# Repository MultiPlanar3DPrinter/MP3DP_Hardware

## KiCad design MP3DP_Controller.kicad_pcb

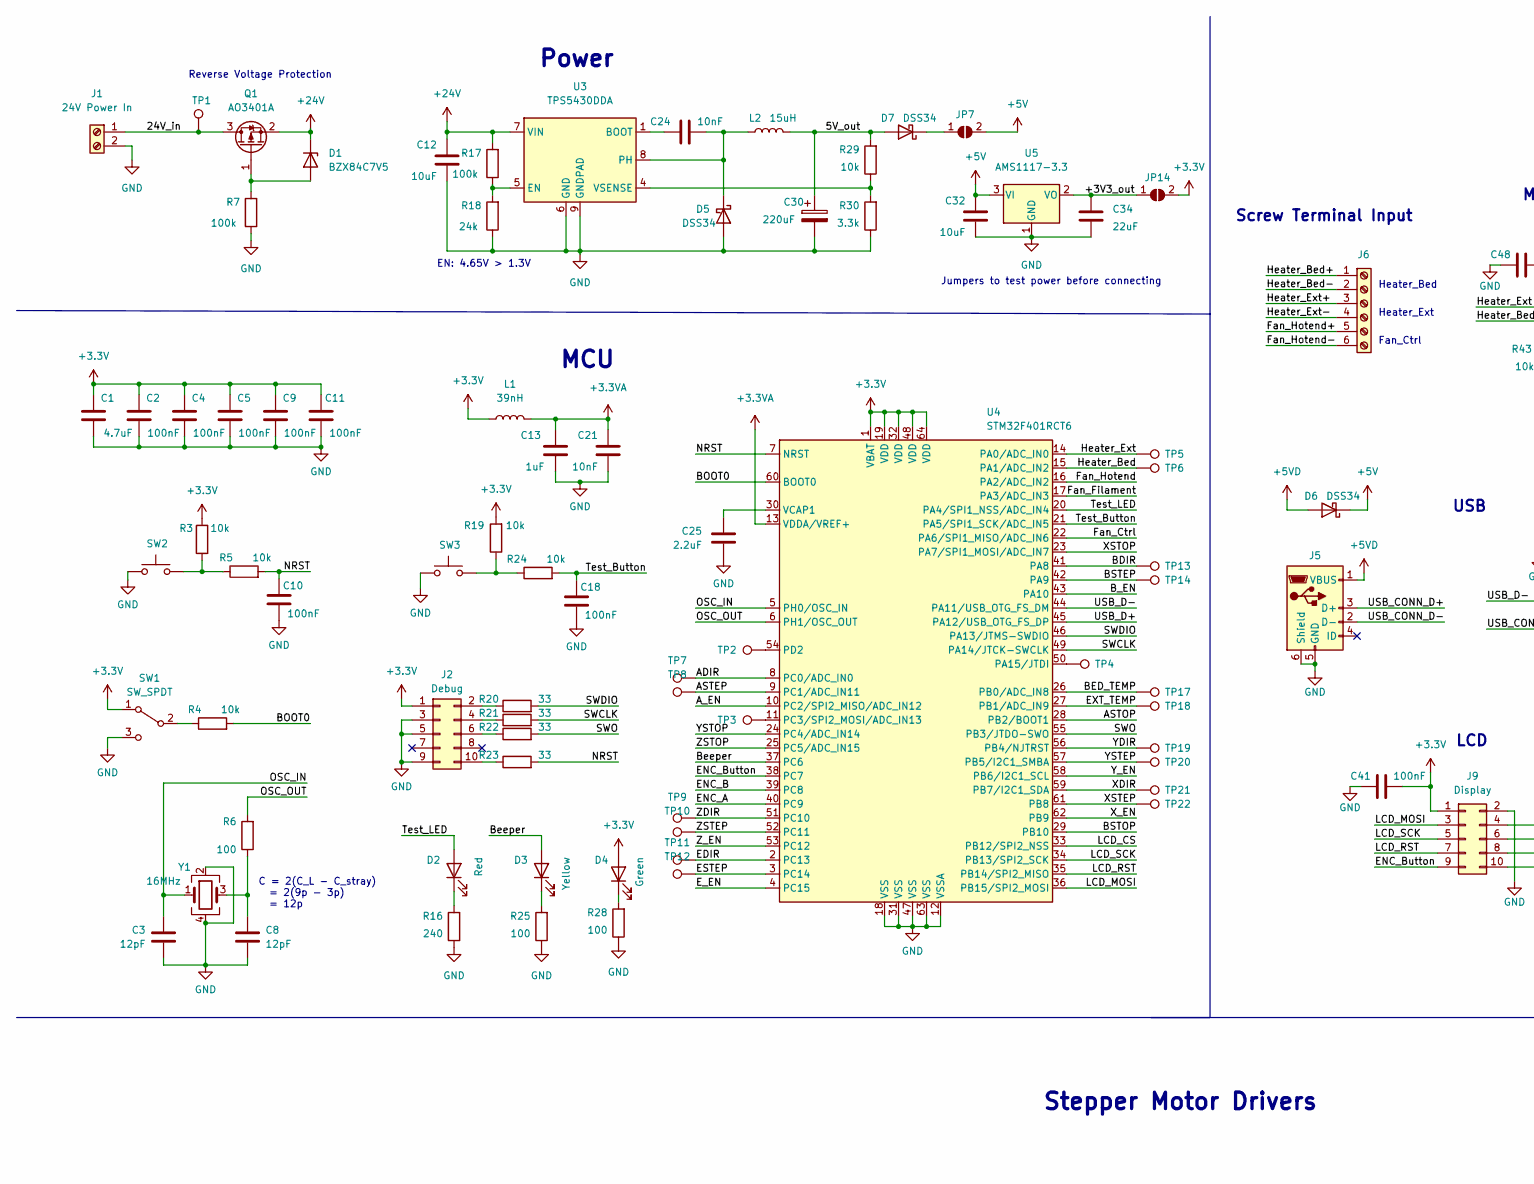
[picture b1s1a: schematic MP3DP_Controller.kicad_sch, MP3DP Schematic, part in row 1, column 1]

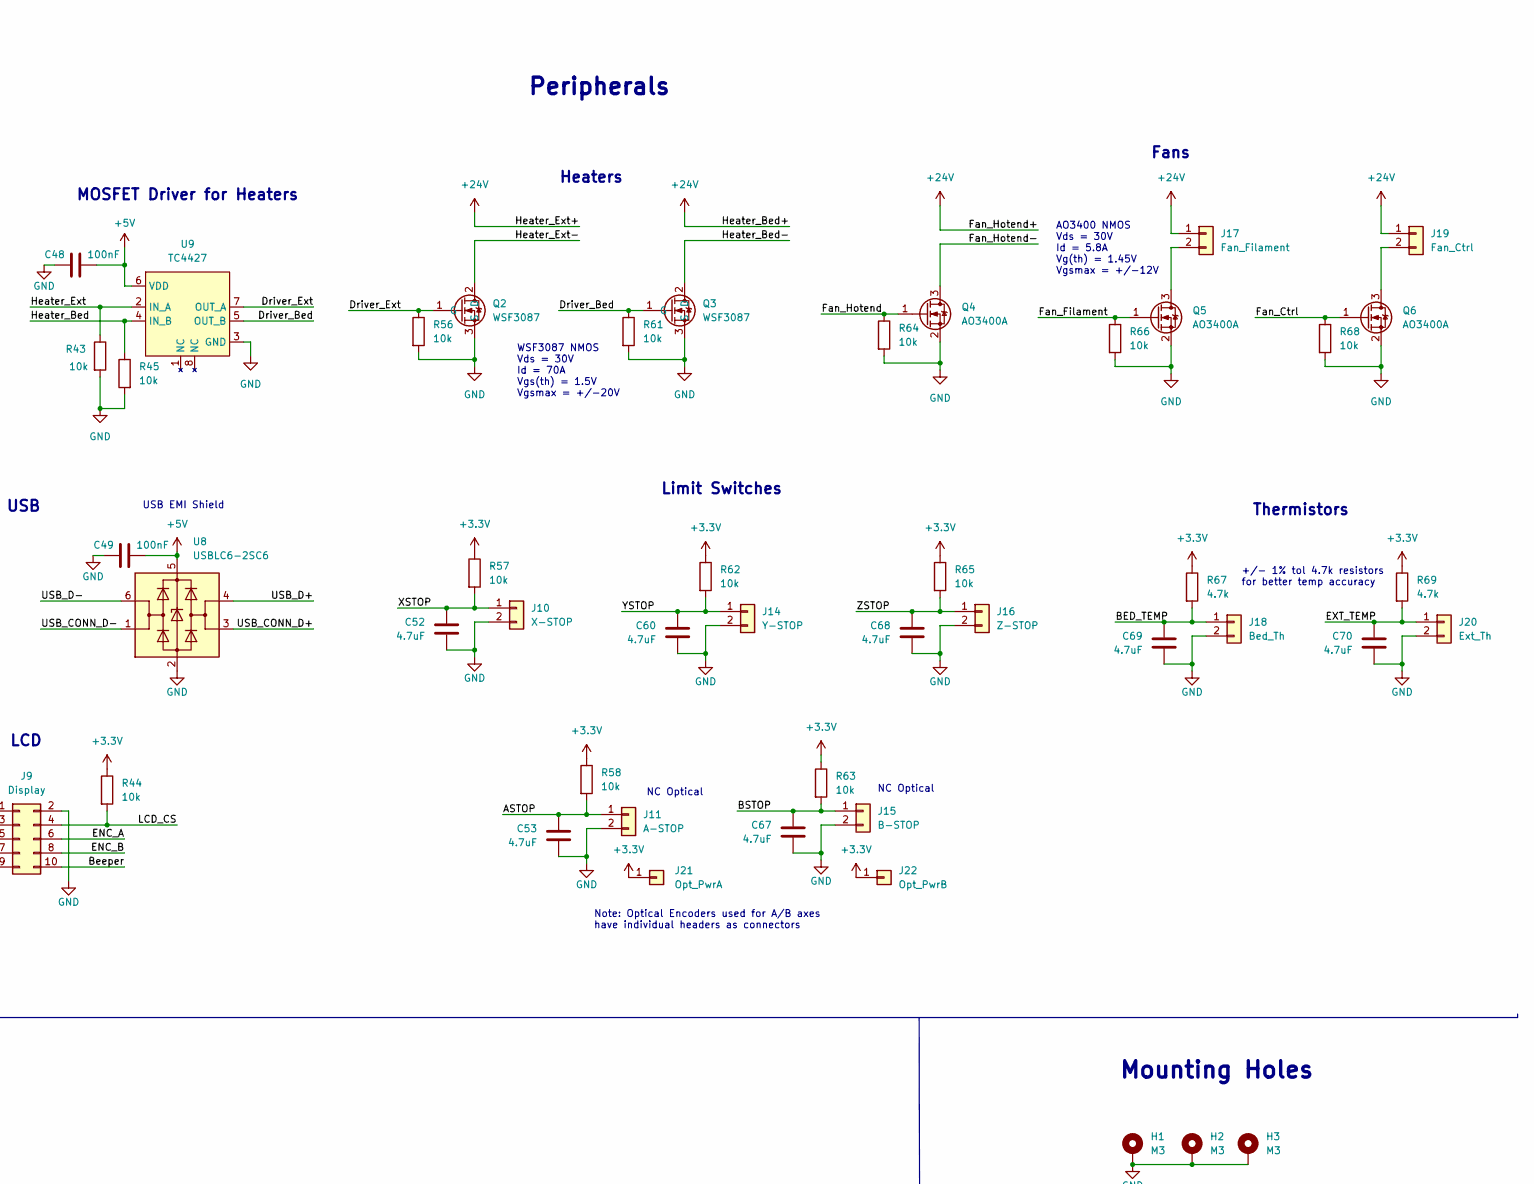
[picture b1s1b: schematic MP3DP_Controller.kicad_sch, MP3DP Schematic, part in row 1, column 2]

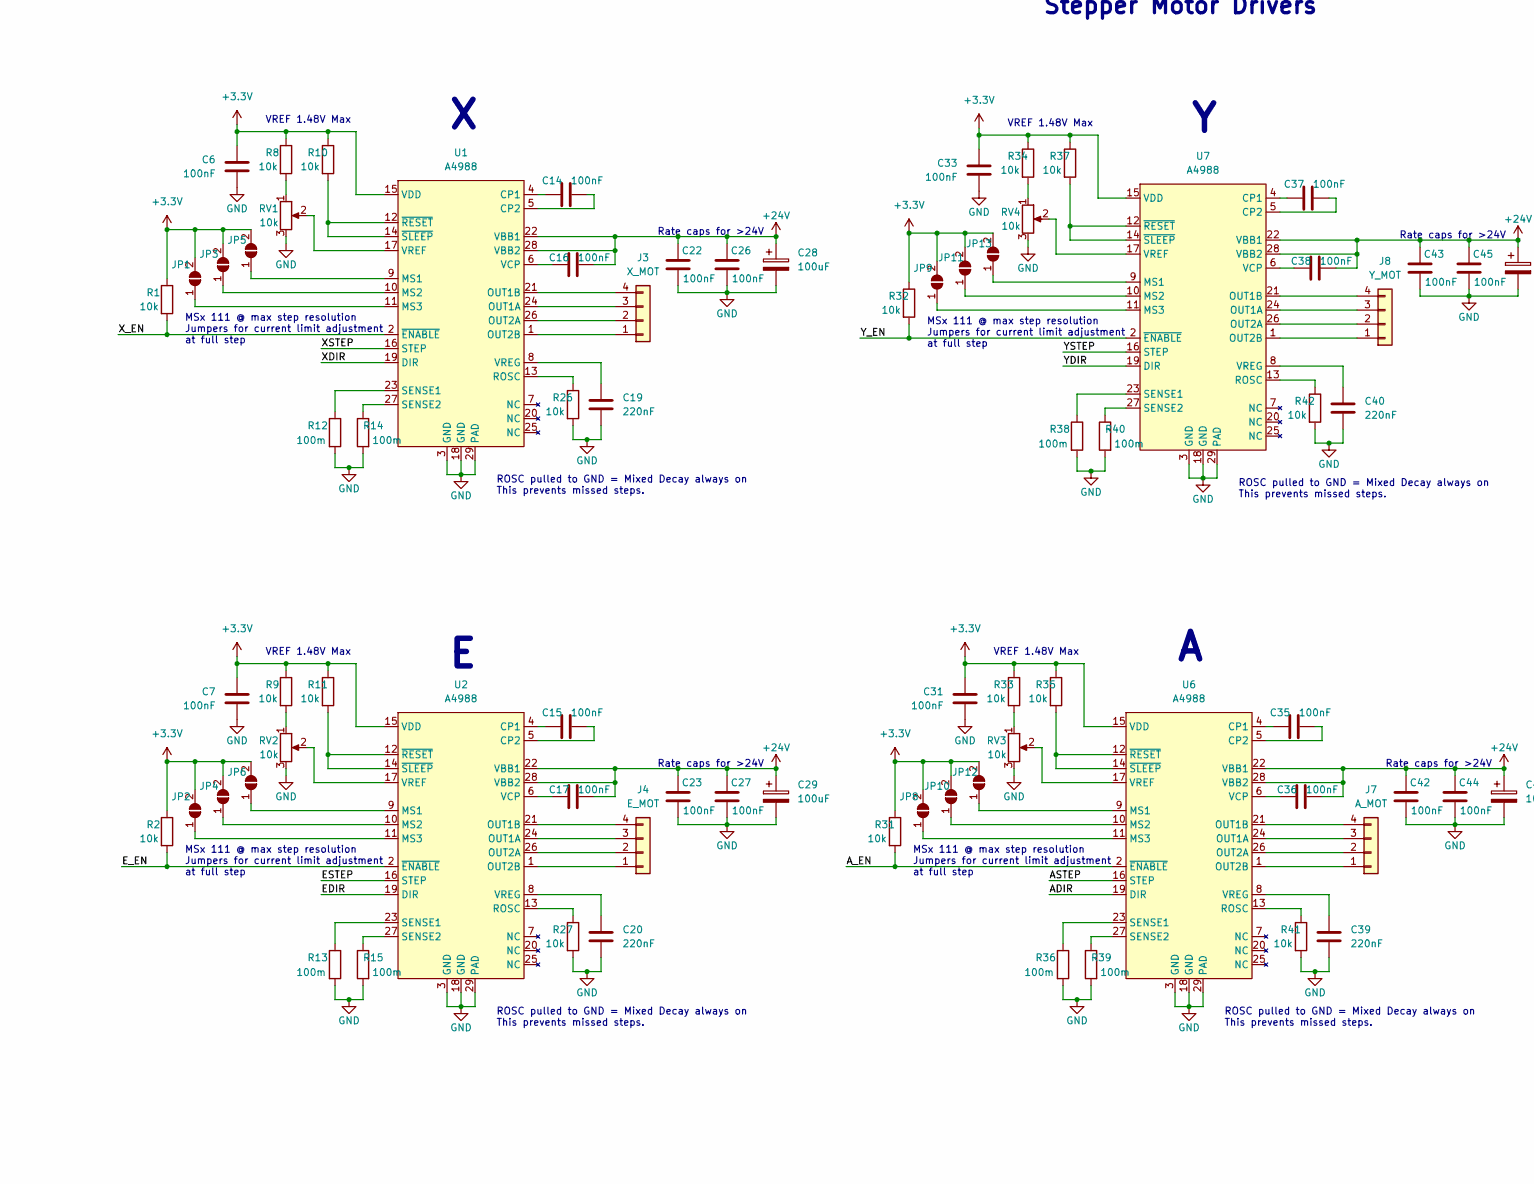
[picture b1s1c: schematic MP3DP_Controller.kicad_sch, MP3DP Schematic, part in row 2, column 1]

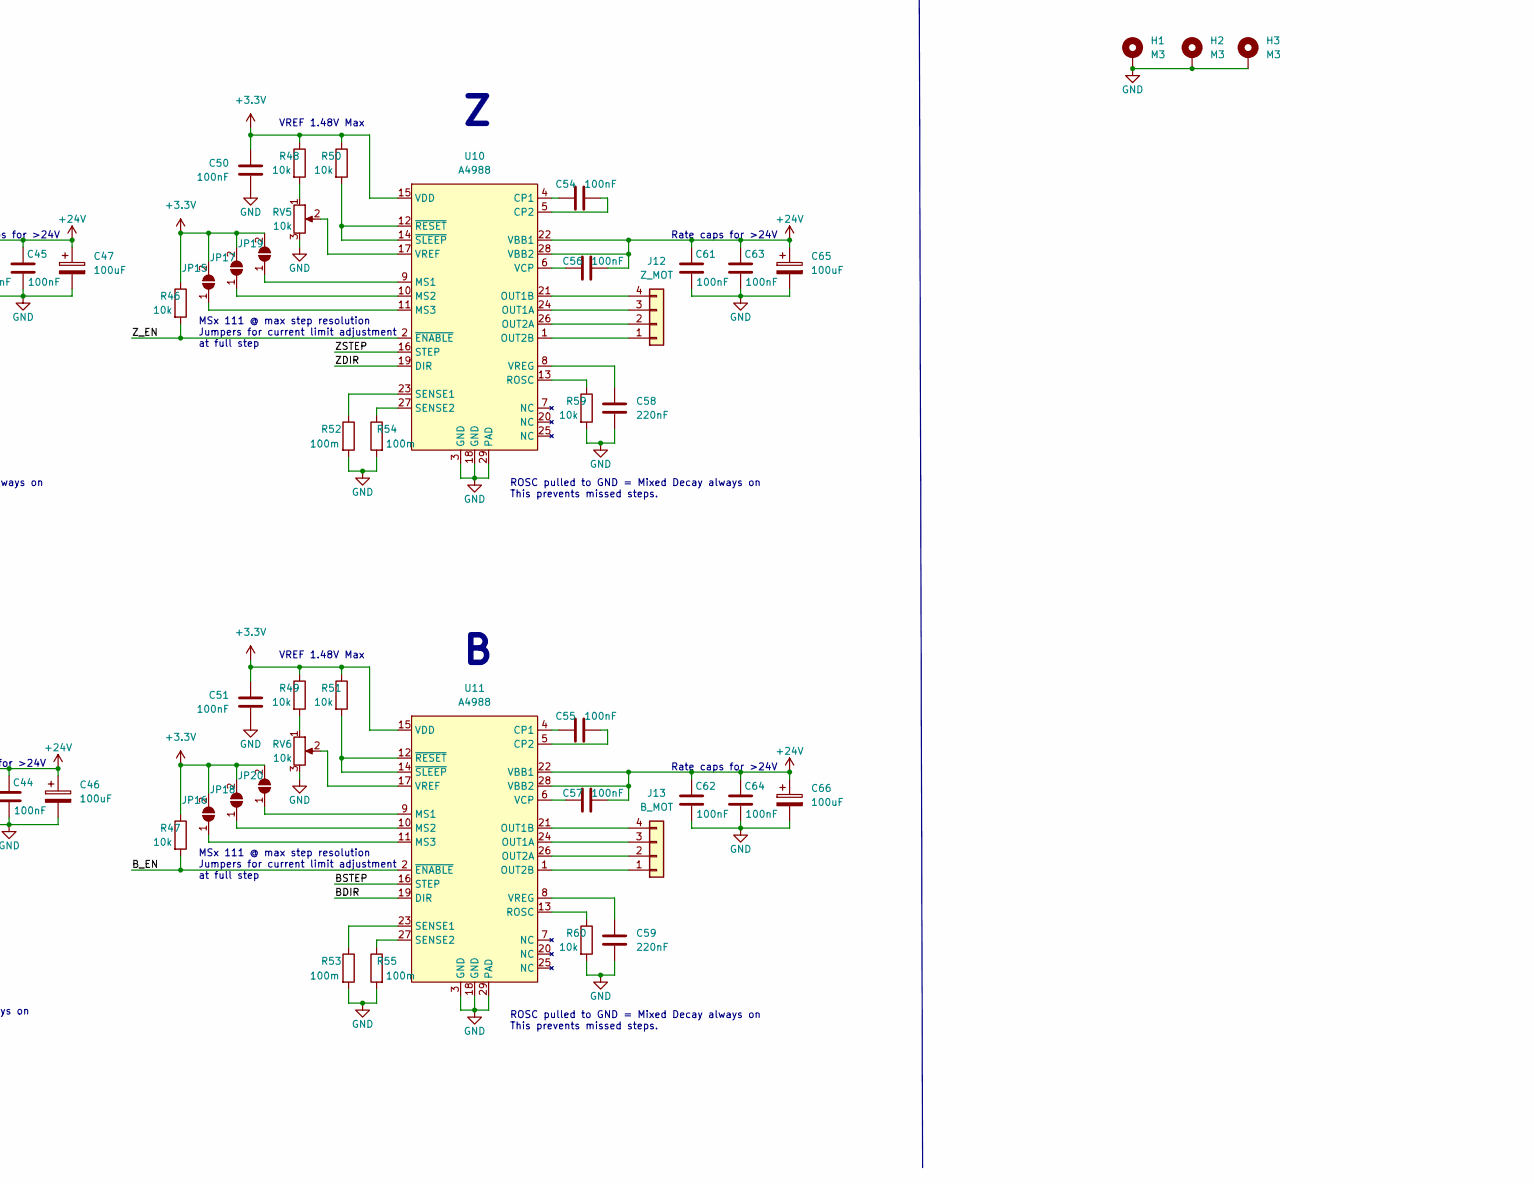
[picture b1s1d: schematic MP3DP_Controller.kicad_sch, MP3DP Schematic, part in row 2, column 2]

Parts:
C1, C52, C53, C60, C67, C68, C69, C70: 4.7uF; C_0603_1608Metric; MFR Part# C1608X5R1V475KT000E; JLCPCB Part# C329940
C2, C4, C5, C6, C7, C9, C10, C11, C14, C15, C16, C17, C18, C22, C23, C26, C27, C31, C33, C35, C36, C37, C38, C41, C42, C43, C44, C45, C48, C49, C50, C51, C54, C55, C56, C57, C61, C62, C63, C64: 100nF; C_0402_1005Metric; MFR Part# CC0402KRX5R9BB104; JLCPCB Part# C105882
C3, C8: 12pF; C_0402_1005Metric; MFR Part# 0402CG120J500NT; JLCPCB Part# C1547
C12: 10uF; C_0805_2012Metric; MFR Part# C0805X5R106K500NT; JLCPCB Part# C962154
C13: 1uF; C_0402_1005Metric; MFR Part# C0402X5R105K350NT; JLCPCB Part# C968773
C19, C20, C39, C40, C58, C59: 220nF; C_0402_1005Metric; MFR Part# CL10B224KB8NNNC; JLCPCB Part# C64705
C21, C24: 10nF; C_0402_1005Metric; MFR Part# CC0402KRX7R9BB103; JLCPCB Part# C60133
C25: 2.2uF; C_0402_1005Metric; MFR Part# C1005X5R1V225KT000E; JLCPCB Part# C0402
C28, C29, C46, C47, C65, C66: 100uF; CP_Radial_D6.3mm_P2.50mm; MFR Part# 35YXJ100M6.3X11; JLCPCB Part# C88754
C30: 220uF; CP_Radial_D6.3mm_P2.50mm; MFR Part# KM227M016E11RR0VH2FP0; JLCPCB Part# C43349
C32: 10uF; C_0603_1608Metric; MFR Part# GRM188R6YA106MA73D; JLCPCB Part# C194427
C34: 22uF; C_0805_2012Metric; MFR Part# C2012X5R1V226MT000E; JLCPCB Part# C338080
D1: BZX84C7V5; D_SOT-23_ANK; MFR Part# BZX84C7V5; JLCPCB Part# C235743
D2: Red; LED_0603_1608Metric; MFR Part# KT-0603R; JLCPCB Part# C2286
D3: Yellow; LED_0603_1608Metric; MFR Part# SZYY0603W; JLCPCB Part# C434422
D4: Green; LED_0603_1608Metric; MFR Part# D-060306G1/SS2/G1; JLCPCB Part# C118334
D5, D6, D7: DSS34; D_SOD-123F; MFR Part# DSS34; JLCPCB Part# C64982
H1, H2, H3: M3; MountingHole_3.2mm_M3_DIN965_Pad
J1: 24V Power In; TerminalBlock_bornier-2_P5.08mm; MFR Part# KF301-5.0-2P; JLCPCB Part# C474881
J2: Debug; PinHeader_2x05_P2.54mm_Vertical; MFR Part# B-2100S10P-B110; JLCPCB Part# C124387
J3: X_MOT; JST_XH_B4B-XH-A_1x04_P2.50mm_Vertical; MFR Part# B4B-XH-A(LF)(SN); JLCPCB Part# C144395
J4: E_MOT; JST_XH_B4B-XH-A_1x04_P2.50mm_Vertical; MFR Part# B4B-XH-A(LF)(SN); JLCPCB Part# C144395
J5: Amphenol; USB_Micro-B_Amphenol_10118194_Horizontal; MFR Part# 10118194-0001LF; JLCPCB Part# C132563
J6: Screw_Terminal_01x06; TerminalBlock_bornier-6_P5.08mm; MFR Part# WJ126V-5.0-6P; JLCPCB Part# C8379
J7: A_MOT; JST_XH_B4B-XH-A_1x04_P2.50mm_Vertical; MFR Part# B4B-XH-A(LF)(SN); JLCPCB Part# C144395
J8: Y_MOT; JST_XH_B4B-XH-A_1x04_P2.50mm_Vertical; MFR Part# B4B-XH-A(LF)(SN); JLCPCB Part# C144395
J9: Display; IDC-Header_2x05_P2.54mm_Vertical; MFR Part# 321010SG0ABK00A01; JLCPCB Part# C429962
J10: X-STOP; JST_XH_B2B-XH-A_1x02_P2.50mm_Vertical; MFR Part# B2B-XH-A(LF)(SN); JLCPCB Part# C158012
J11: A-STOP; JST_XH_B2B-XH-A_1x02_P2.50mm_Vertical; MFR Part# B2B-XH-A(LF)(SN); JLCPCB Part# C158012
J12: Z_MOT; JST_XH_B4B-XH-A_1x04_P2.50mm_Vertical; MFR Part# B4B-XH-A(LF)(SN); JLCPCB Part# C144395
J13: B_MOT; JST_XH_B4B-XH-A_1x04_P2.50mm_Vertical; MFR Part# B4B-XH-A(LF)(SN); JLCPCB Part# C144395
J14: Y-STOP; JST_XH_B2B-XH-A_1x02_P2.50mm_Vertical; MFR Part# B2B-XH-A(LF)(SN); JLCPCB Part# C158012
J15: B-STOP; JST_XH_B2B-XH-A_1x02_P2.50mm_Vertical; MFR Part# B2B-XH-A(LF)(SN); JLCPCB Part# C158012
J16: Z-STOP; JST_XH_B2B-XH-A_1x02_P2.50mm_Vertical; MFR Part# B2B-XH-A(LF)(SN); JLCPCB Part# C158012
J17: Fan_Filament; JST_XH_B2B-XH-A_1x02_P2.50mm_Vertical; MFR Part# B2B-XH-A(LF)(SN); JLCPCB Part# C158012
J18: Bed_Th; JST_XH_B2B-XH-A_1x02_P2.50mm_Vertical; MFR Part# B2B-XH-A(LF)(SN); JLCPCB Part# C158012
J19: Fan_Ctrl; JST_XH_B2B-XH-A_1x02_P2.50mm_Vertical; MFR Part# B2B-XH-A(LF)(SN); JLCPCB Part# C158012
J20: Ext_Th; JST_XH_B2B-XH-A_1x02_P2.50mm_Vertical; MFR Part# B2B-XH-A(LF)(SN); JLCPCB Part# C158012
J21: Opt_PwrA; PinHeader_1x01_P2.54mm_Vertical; MFR Part# PH-00676; JLCPCB Part# C2685179
J22: Opt_PwrB; PinHeader_1x01_P2.54mm_Vertical; MFR Part# PH-00676; JLCPCB Part# C2685179
JP1, JP2, JP3, JP4, JP5, JP6, JP7, JP8, JP9, JP10, JP11, JP12, JP13, JP14, JP15, JP16, JP17, JP18, JP19, JP20: SolderJumper_2_Open; SolderJumper-2_P1.3mm_Open_TrianglePad1.0x1.5mm
L1: 39nH; L_0603_1608Metric; MFR Part# SDCL1608C39NJTDF; JLCPCB Part# C74308
L2: 15uH; L_Taiyo-Yuden_MD-5050; MFR Part# SMNR5040-150MT; JLCPCB Part# C135291
Q1: AO3401A; SOT-23; MFR Part# AO3401A; JLCPCB Part# C15127
Q2, Q3: WSF3087; TO-252-3_TabPin2; MFR Part# WSF3087; JLCPCB Part# C2758420
Q4, Q5, Q6: AO3400A; SOT-23; MFR Part# AO3400A; JLCPCB Part# C20917
R1, R2, R3, R4, R5, R8, R9, R10, R11, R19, R24, R26, R27, R29, R31, R32, R33, R34, R35, R37, R41, R42, R43, R44, R45, R46, R47, R48, R49, R50, R51, R56, R57, R58, R59, R60, R61, R62, R63, R64, R65, R66, R68: 10k; R_0402_1005Metric; MFR Part# AC0402FR-0710KL; JLCPCB Part# C144807
R6, R25, R28: 100; R_0402_1005Metric; MFR Part# RC0402FR-07100RL; JLCPCB Part# C106232
R7, R17: 100k; R_0402_1005Metric; MFR Part# AC0402JR-07100KL; JLCPCB Part# C144732
R12, R13, R14, R15, R36, R38, R39, R40, R52, R53, R54, R55: 100m; R_0603_1608Metric; MFR Part# 0603WAJ010KT5E; JLCPCB Part# C247025
R16: 240; R_0402_1005Metric; MFR Part# RK73B1ETTP241J; JLCPCB Part# C131545
R18: 24k; R_0402_1005Metric; MFR Part# AC0402FR-0724KL; JLCPCB Part# C144775
R20, R21, R22, R23: 33; R_0402_1005Metric; MFR Part# RC0402FR-0733RL; JLCPCB Part# C138002
R30: 3.3k; R_0402_1005Metric; MFR Part# RC0402FR-073K3L; JLCPCB Part# C137992
R67, R69: 4.7k; R_0402_1005Metric; MFR Part# RC0402FR-074K7L; JLCPCB Part# C105871
RV1, RV2, RV3, RV4, RV5, RV6: 10k; Potentiometer_Bourns_3224W_Vertical; MFR Part# 3224W-1-103E; JLCPCB Part# C81348
SW1: SW_SPDT; SW_SPDT_PCM12; MFR Part# PCM12SMTR; JLCPCB Part# C221841
SW2, SW3: SW_Push; SW_SPST_B3U-1000P; MFR Part# B3U-1000P; JLCPCB Part# C231329
TP1, TP2, TP3, TP4, TP5, TP6, TP7, TP8, TP9, TP10, TP11, TP12, TP13, TP14, TP17, TP18, TP19, TP20, TP21, TP22: TestPoint; TestPoint_Pad_D2.0mm
U1, U2, U6, U7, U10, U11: A4988; QFN-28-1EP_5x5mm_P0.5mm_EP3.35x3.35mm_ThermalVias; MFR Part# A4988SETTR-T; JLCPCB Part# C38437
U3: TPS5430DDA; TI_SO-PowerPAD-8_ThermalVias; MFR Part# TPS5430DDAR; JLCPCB Part# C9864
U4: STM32F401RCT6; LQFP-64_10x10mm_P0.5mm; MFR Part# STM32F401RCT6; JLCPCB Part# C74524
U5: AMS1117-3.3; SOT-223-3_TabPin2; MFR Part# AMS1117-3.3; JLCPCB Part# C6186
U8: USBLC6-2SC6; SOT-23-6; MFR Part# USBLC6-2SC6; JLCPCB Part# C2827654
U9: TC4427; SOIC-8-1EP_3.9x4.9mm_P1.27mm_EP2.29x3mm; MFR Part# TC4427AEOA713; JLCPCB Part# C20551
Y1: 16MHz; Crystal_SMD_3225-4Pin_3.2x2.5mm; MFR Part# X322516MLB4SI; JLCPCB Part# C13738

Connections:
+3.3VA: C13.2, C21.2, L1.2, U4.13 (VDDA/VREF+)
+3V3: C1.2, C2.2, C4.2, C5.2, C6.2, C7.2, C9.2, C11.2, C31.2, C33.2, C41.1, C50.2, C51.2, D4.2 (A), J2.1, J9.1, J21.1, J22.1, JP1.2 (B), JP2.2 (B), JP3.2 (B), JP4.2 (B), JP5.2 (B), JP6.2 (B), JP8.2 (B), JP9.2 (B), JP10.2 (B), JP11.2 (B), JP12.2 (B), JP13.2 (B), JP14.2 (B), JP15.2 (B), JP16.2 (B), JP17.2 (B), JP18.2 (B), JP19.2 (B), JP20.2 (B), L1.1, R1.1, R2.1, R3.2, R8.1, R9.1, R10.1, R11.1, R19.2, R31.1, R32.1, R33.1, R34.1, R35.1, R37.1, R44.1, R46.1, R47.1, R48.1, R49.1, R50.1, R51.1, R57.1, R58.1, R62.1, R63.1, R65.1, R67.1, R69.1, SW1.1 (A), U1.15 (VDD), U2.15 (VDD), U4.1 (VBAT), U4.19 (VDD), U4.32 (VDD), U4.48 (VDD), U4.64 (VDD), U6.15 (VDD), U7.15 (VDD), U10.15 (VDD), U11.15 (VDD)
+5V: C32.2, C48.1, C49.1, D6.1 (K), JP7.2 (B), U5.3 (VI), U8.5 (VBUS), U9.6 (VDD)
+5VD: D6.2 (A), J5.1 (VBUS)
+24V: C12.2, C16.1, C17.1, C22.1, C23.1, C26.1, C27.1, C28.1, C29.1, C36.1, C38.1, C42.1, C43.1, C44.1, C45.1, C46.1, C47.1, C56.1, C57.1, C61.1, C62.1, C63.1, C64.1, C65.1, C66.1, D1.1 (K), J6.1, J6.3, J6.5, J17.1, J19.1, Q1.2 (S), R17.2, U1.22 (VBB1), U1.28 (VBB2), U2.22 (VBB1), U2.28 (VBB2), U3.7 (VIN), U6.22 (VBB1), U6.28 (VBB2), U7.22 (VBB1), U7.28 (VBB2), U10.22 (VBB1), U10.28 (VBB2), U11.22 (VBB1), U11.28 (VBB2)
/5V_out: C30.1, D7.2 (A), L2.2, R29.2
/24V_in: J1.1, Q1.3 (D), TP1.1
/+3V3_out: C34.2, JP14.1 (A), U5.2 (VO)
/ADIR: TP7.1, U4.8 (PC0/ADC_IN0), U6.19 (DIR)
/ASTEP: TP8.1, U4.9 (PC1/ADC_IN11), U6.16 (STEP)
/ASTOP: C53.2, J11.1, R58.2, U4.28 (PB2/BOOT1)
/A_EN: R31.2, U4.10 (PC2/SPI2_MISO/ADC_IN12), U6.2 (~ENABLE)
/BDIR: TP13.1, U4.41 (PA8), U11.19 (DIR)
/BED_TEMP: C69.2, J18.1, R67.2, TP17.1, U4.26 (PB0/ADC_IN8)
/BOOT0: R4.2, U4.60 (BOOT0)
/BSTEP: TP14.1, U4.42 (PA9), U11.16 (STEP)
/BSTOP: C67.2, J15.1, R63.2, U4.29 (PB10)
/B_EN: R47.2, U4.43 (PA10), U11.2 (~ENABLE)
/Beeper: D3.2 (A), J9.10, U4.37 (PC6)
/Driver_Bed: Q3.1 (G), R61.1, U9.5 (OUT_B)
/Driver_Ext: Q2.1 (G), R56.1, U9.7 (OUT_A)
/EDIR: TP11.1, U2.19 (DIR), U4.2 (PC13)
/ENC_A: J9.6, U4.40 (PC9)
/ENC_B: J9.8, U4.39 (PC8)
/ENC_Button: J9.9, U4.38 (PC7)
/ESTEP: TP12.1, U2.16 (STEP), U4.3 (PC14)
/EXT_TEMP: C70.2, J20.1, R69.2, TP18.1, U4.27 (PB1/ADC_IN9)
/E_EN: R2.2, U2.2 (~ENABLE), U4.4 (PC15)
/Fan_Ctrl: Q6.1 (G), R68.1, U4.22 (PA6/SPI1_MISO/ADC_IN6)
/Fan_Filament: Q5.1 (G), R66.1, U4.17 (PA3/ADC_IN3)
/Fan_Hotend: Q4.1 (G), R64.1, U4.16 (PA2/ADC_IN2)
/Fan_Hotend-: J6.6, Q4.3 (D)
/Heater_Bed: R45.1, TP6.1, U4.15 (PA1/ADC_IN2), U9.4 (IN_B)
/Heater_Bed-: J6.2, Q3.2 (D)
/Heater_Ext: R43.1, TP5.1, U4.14 (PA0/ADC_IN0), U9.2 (IN_A)
/Heater_Ext-: J6.4, Q2.2 (D)
/LCD_CS: J9.4, R44.2, U4.33 (PB12/SPI2_NSS)
/LCD_MOSI: J9.3, U4.36 (PB15/SPI2_MOSI)
/LCD_RST: J9.7, U4.35 (PB14/SPI2_MISO)
/LCD_SCK: J9.5, U4.34 (PB13/SPI2_SCK)
/NRST: C10.2, R5.2, R23.2, U4.7 (NRST)
/OSC_IN: C3.2, U4.5 (PH0/OSC_IN), Y1.1
/OSC_OUT: R6.2, U4.6 (PH1/OSC_OUT)
/SWCLK: R21.2, U4.49 (PA14/JTCK-SWCLK)
/SWDIO: R20.2, U4.46 (PA13/JTMS-SWDIO)
/SWO: R22.2, U4.55 (PB3/JTDO-SWO)
/Test_Button: C18.2, R24.2, U4.21 (PA5/SPI1_SCK/ADC_IN5)
/Test_LED: D2.2 (A), U4.20 (PA4/SPI1_NSS/ADC_IN4)
/USB_CONN_D+: J5.3 (D+), U8.3 (I/O2)
/USB_CONN_D-: J5.2 (D-), U8.1 (I/O1)
/USB_D+: U4.45 (PA12/USB_OTG_FS_DP), U8.4 (I/O2)
/USB_D-: U4.44 (PA11/USB_OTG_FS_DM), U8.6 (I/O1)
/XDIR: TP21.1, U1.19 (DIR), U4.59 (PB7/I2C1_SDA)
/XSTEP: TP22.1, U1.16 (STEP), U4.61 (PB8)
/XSTOP: C52.2, J10.1, R57.2, U4.23 (PA7/SPI1_MOSI/ADC_IN7)
/X_EN: R1.2, U1.2 (~ENABLE), U4.62 (PB9)
/YDIR: TP19.1, U4.56 (PB4/NJTRST), U7.19 (DIR)
/YSTEP: TP20.1, U4.57 (PB5/I2C1_SMBA), U7.16 (STEP)
/YSTOP: C60.2, J14.1, R62.2, U4.24 (PC4/ADC_IN14)
/Y_EN: R32.2, U4.58 (PB6/I2C1_SCL), U7.2 (~ENABLE)
/ZDIR: TP9.1, U4.51 (PC10), U10.19 (DIR)
/ZSTEP: TP10.1, U4.52 (PC11), U10.16 (STEP)
/ZSTOP: C68.2, J16.1, R65.2, U4.25 (PC5/ADC_IN15)
/Z_EN: R46.2, U4.53 (PC12), U10.2 (~ENABLE)
GND: C1.1, C2.1, C3.1, C4.1, C5.1, C6.1, C7.1, C8.1, C9.1, C10.1, C11.1, C12.1, C13.1, C18.1, C19.1, C20.1, C21.1, C22.2, C23.2, C25.1, C26.2, C27.2, C28.2, C29.2, C30.2, C31.1, C32.1, C33.1, C34.1, C39.1, C40.1, C41.2, C42.2, C43.2, C44.2, C45.2, C46.2, C47.2, C48.2, C49.2, C50.1, C51.1, C52.1, C53.1, C58.1, C59.1, C60.1, C61.2, C62.2, C63.2, C64.2, C65.2, C66.2, C67.1, C68.1, C69.1, C70.1, D5.2 (A), H1.1, H2.1, H3.1, J1.2, J2.3, J2.5, J2.9, J5.5 (GND), J5.6 (Shield), J9.2, J10.2, J11.2, J14.2, J15.2, J16.2, J18.2, J20.2, Q2.3 (S), Q3.3 (S), Q4.2 (S), Q5.2 (S), Q6.2 (S), R7.1, R12.2, R13.2, R14.2, R15.2, R16.1, R18.1, R25.1, R26.2, R27.2, R28.1, R30.1, R36.2, R38.2, R39.2, R40.2, R41.2, R42.2, R43.2, R45.2, R52.2, R53.2, R54.2, R55.2, R56.2, R59.2, R60.2, R61.2, R64.2, R66.2, R68.2, RV1.3, RV2.3, RV3.3, RV4.3, RV5.3, RV6.3, SW1.3 (C), SW2.1, SW3.1, U1.3 (GND), U1.18 (GND), U1.29 (PAD), U2.3 (GND), U2.18 (GND), U2.29 (PAD), U3.6 (GND), U3.9 (GNDPAD), U4.12 (VSSA), U4.18 (VSS), U4.31 (VSS), U4.47 (VSS), U4.63 (VSS), U5.1 (GND), U6.3 (GND), U6.18 (GND), U6.29 (PAD), U7.3 (GND), U7.18 (GND), U7.29 (PAD), U8.2 (GND), U9.3 (GND), U10.3 (GND), U10.18 (GND), U10.29 (PAD), U11.3 (GND), U11.18 (GND), U11.29 (PAD), Y1.2, Y1.4
unnamed: C8.2, R6.1, Y1.3
unnamed: C14.1, U1.5 (CP2)
unnamed: C14.2, U1.4 (CP1)
unnamed: C15.1, U2.5 (CP2)
unnamed: C15.2, U2.4 (CP1)
unnamed: C16.2, U1.6 (VCP)
unnamed: C17.2, U2.6 (VCP)
unnamed: C19.2, U1.8 (VREG)
unnamed: C20.2, U2.8 (VREG)
unnamed: C24.1, D5.1 (K), L2.1, U3.8 (PH)
unnamed: C24.2, U3.1 (BOOT)
unnamed: C25.2, U4.30 (VCAP1)
unnamed: C35.1, U6.5 (CP2)
unnamed: C35.2, U6.4 (CP1)
unnamed: C36.2, U6.6 (VCP)
unnamed: C37.1, U7.5 (CP2)
unnamed: C37.2, U7.4 (CP1)
unnamed: C38.2, U7.6 (VCP)
unnamed: C39.2, U6.8 (VREG)
unnamed: C40.2, U7.8 (VREG)
unnamed: C54.1, U10.5 (CP2)
unnamed: C54.2, U10.4 (CP1)
unnamed: C55.1, U11.5 (CP2)
unnamed: C55.2, U11.4 (CP1)
unnamed: C56.2, U10.6 (VCP)
unnamed: C57.2, U11.6 (VCP)
unnamed: C58.2, U10.8 (VREG)
unnamed: C59.2, U11.8 (VREG)
unnamed: D1.2 (A), Q1.1 (G), R7.2
unnamed: D2.1 (K), R16.2
unnamed: D3.1 (K), R25.2
unnamed: D4.1 (K), R28.2
unnamed: D7.1 (K), JP7.1 (A)
unnamed: J2.2, R20.1
unnamed: J2.4, R21.1
unnamed: J2.6, R22.1
unnamed: J2.10, R23.1
unnamed: J3.1, U1.1 (OUT2B)
unnamed: J3.2, U1.26 (OUT2A)
unnamed: J3.3, U1.24 (OUT1A)
unnamed: J3.4, U1.21 (OUT1B)
unnamed: J4.1, U2.1 (OUT2B)
unnamed: J4.2, U2.26 (OUT2A)
unnamed: J4.3, U2.24 (OUT1A)
unnamed: J4.4, U2.21 (OUT1B)
unnamed: J7.1, U6.1 (OUT2B)
unnamed: J7.2, U6.26 (OUT2A)
unnamed: J7.3, U6.24 (OUT1A)
unnamed: J7.4, U6.21 (OUT1B)
unnamed: J8.1, U7.1 (OUT2B)
unnamed: J8.2, U7.26 (OUT2A)
unnamed: J8.3, U7.24 (OUT1A)
unnamed: J8.4, U7.21 (OUT1B)
unnamed: J12.1, U10.1 (OUT2B)
unnamed: J12.2, U10.26 (OUT2A)
unnamed: J12.3, U10.24 (OUT1A)
unnamed: J12.4, U10.21 (OUT1B)
unnamed: J13.1, U11.1 (OUT2B)
unnamed: J13.2, U11.26 (OUT2A)
unnamed: J13.3, U11.24 (OUT1A)
unnamed: J13.4, U11.21 (OUT1B)
unnamed: J17.2, Q5.3 (D)
unnamed: J19.2, Q6.3 (D)
unnamed: JP1.1 (A), U1.11 (MS3)
unnamed: JP2.1 (A), U2.11 (MS3)
unnamed: JP3.1 (A), U1.10 (MS2)
unnamed: JP4.1 (A), U2.10 (MS2)
unnamed: JP5.1 (A), U1.9 (MS1)
unnamed: JP6.1 (A), U2.9 (MS1)
unnamed: JP8.1 (A), U6.11 (MS3)
unnamed: JP9.1 (A), U7.11 (MS3)
unnamed: JP10.1 (A), U6.10 (MS2)
unnamed: JP11.1 (A), U7.10 (MS2)
unnamed: JP12.1 (A), U6.9 (MS1)
unnamed: JP13.1 (A), U7.9 (MS1)
unnamed: JP15.1 (A), U10.11 (MS3)
unnamed: JP16.1 (A), U11.11 (MS3)
unnamed: JP17.1 (A), U10.10 (MS2)
unnamed: JP18.1 (A), U11.10 (MS2)
unnamed: JP19.1 (A), U10.9 (MS1)
unnamed: JP20.1 (A), U11.9 (MS1)
unnamed: R3.1, R5.1, SW2.2
unnamed: R4.1, SW1.2 (B)
unnamed: R8.2, RV1.1
unnamed: R9.2, RV2.1
unnamed: R10.2, U1.12 (~RESET), U1.14 (~SLEEP)
unnamed: R11.2, U2.12 (~RESET), U2.14 (~SLEEP)
unnamed: R12.1, U1.23 (SENSE1)
unnamed: R13.1, U2.23 (SENSE1)
unnamed: R14.1, U1.27 (SENSE2)
unnamed: R15.1, U2.27 (SENSE2)
unnamed: R17.1, R18.2, U3.5 (EN)
unnamed: R19.1, R24.1, SW3.2
unnamed: R26.1, U1.13 (ROSC)
unnamed: R27.1, U2.13 (ROSC)
unnamed: R29.1, R30.2, U3.4 (VSENSE)
unnamed: R33.2, RV3.1
unnamed: R34.2, RV4.1
unnamed: R35.2, U6.12 (~RESET), U6.14 (~SLEEP)
unnamed: R36.1, U6.23 (SENSE1)
unnamed: R37.2, U7.12 (~RESET), U7.14 (~SLEEP)
unnamed: R38.1, U7.23 (SENSE1)
unnamed: R39.1, U6.27 (SENSE2)
unnamed: R40.1, U7.27 (SENSE2)
unnamed: R41.1, U6.13 (ROSC)
unnamed: R42.1, U7.13 (ROSC)
unnamed: R48.2, RV5.1
unnamed: R49.2, RV6.1
unnamed: R50.2, U10.12 (~RESET), U10.14 (~SLEEP)
unnamed: R51.2, U11.12 (~RESET), U11.14 (~SLEEP)
unnamed: R52.1, U10.23 (SENSE1)
unnamed: R53.1, U11.23 (SENSE1)
unnamed: R54.1, U10.27 (SENSE2)
unnamed: R55.1, U11.27 (SENSE2)
unnamed: R59.1, U10.13 (ROSC)
unnamed: R60.1, U11.13 (ROSC)
unnamed: RV1.2, U1.17 (VREF)
unnamed: RV2.2, U2.17 (VREF)
unnamed: RV3.2, U6.17 (VREF)
unnamed: RV4.2, U7.17 (VREF)
unnamed: RV5.2, U10.17 (VREF)
unnamed: RV6.2, U11.17 (VREF)
unnamed: TP2.1, U4.54 (PD2)
unnamed: TP3.1, U4.11 (PC3/SPI2_MOSI/ADC_IN13)
unnamed: TP4.1, U4.50 (PA15/JTDI)

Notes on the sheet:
MSx 111 @ max step resolution Jumpers for current limit adjustment at full step
VREF 1.48V Max
ROSC pulled to GND = Mixed Decay always on This prevents missed steps.
EN: 4.65V > 1.3V
USB
Mounting Holes
Heater_Bed
MOSFET Driver for Heaters
LCD
Reverse Voltage Protection
AO3400 NMOS Vds = 30V Id = 5.8A Vg(th) = 1.45V Vgsmax = +/-12V
Rate caps for >24V
WSF3087 NMOS Vds = 30V Id = 70A Vgs(th) = 1.5V Vgsmax = +/-20V
Limit Switches
Power
Stepper Motor Drivers
Fan_Ctrl
NC Optical
USB EMI Shield
Fans
C = 2(C_L - C_stray) = 2(9p - 3p) = 12p
Peripherals
+/- 1% tol 4.7k resistors for better temp accuracy
Thermistors
MCU
Heaters
Note: Optical Encoders used for A/B axes have individual headers as connectors
Heater_Ext
Jumpers to test power before connecting
Screw Terminal Input

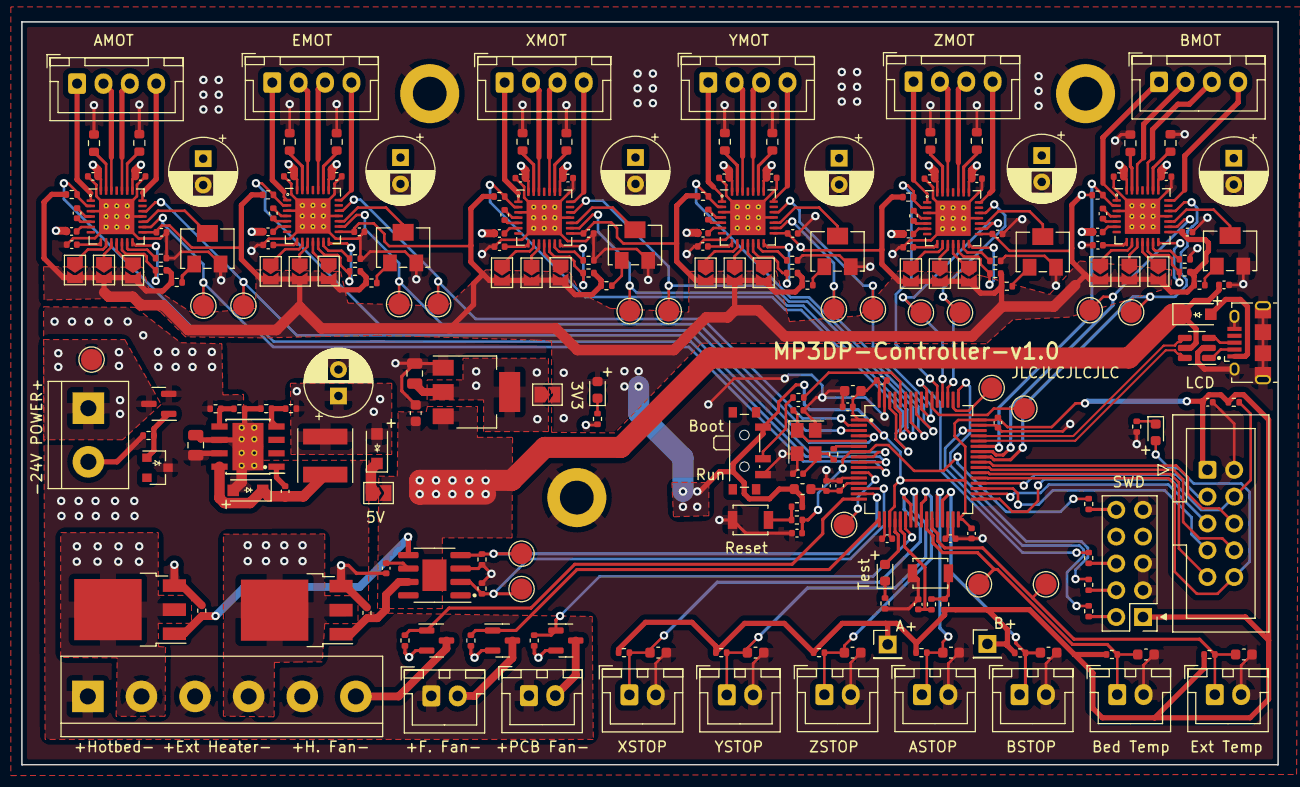
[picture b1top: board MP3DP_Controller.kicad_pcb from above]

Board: 2 copper layers, 119.1 x 70.4 mm, 240 parts (0 on the bottom side), 190 nets.

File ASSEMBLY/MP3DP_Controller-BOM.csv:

"Comment","Designator","Footprint","LCSC"
"4.7uF","C1, C52, C53, C60, C67, C68, C69, C70","Capacitor_SMD:C_0603_1608Metric","C329940"
"100nF","C2, C4, C5, C6, C7, C9, C10, C11, C14, C15, C16, C17, C18, C22, C23, C26, C27, C31, C33, C35, C36, C37, C38, C41, C42, C43, C44, C45, C48, C49, C50, C51, C54, C55, C56, C57, C61, C62, C63, C64","Capacitor_SMD:C_0402_1005Metric","C105882"
"12pF","C3, C8","Capacitor_SMD:C_0402_1005Metric","C1547"
"10uF","C12","Capacitor_SMD:C_0805_2012Metric","C962154"
"1uF","C13","Capacitor_SMD:C_0402_1005Metric","C968773"
"220nF","C19, C20, C39, C40, C58, C59","Capacitor_SMD:C_0402_1005Metric","C64705"
"10nF","C21, C24","Capacitor_SMD:C_0402_1005Metric","C60133"
"2.2uF","C25","Capacitor_SMD:C_0402_1005Metric","C0402"
"100uF","C28, C29, C46, C47, C65, C66","Capacitor_THT:CP_Radial_D6.3mm_P2.50mm","C88754"
"220uF","C30","Capacitor_THT:CP_Radial_D6.3mm_P2.50mm","C43349"
"10uF","C32","Capacitor_SMD:C_0603_1608Metric","C194427"
"22uF","C34","Capacitor_SMD:C_0805_2012Metric","C338080"
"BZX84C7V5","D1","Diode_SMD:D_SOT-23_ANK","C235743"
"Red","D2","LED_SMD:LED_0603_1608Metric","C2286"
"Yellow","D3","LED_SMD:LED_0603_1608Metric","C434422"
"Green","D4","LED_SMD:LED_0603_1608Metric","C118334"
"DSS34","D5, D6, D7","Diode_SMD:D_SOD-123F","C64982"
"M3","H1, H2, H3","MountingHole:MountingHole_3.2mm_M3_DIN965_Pad",""
"24V Power In","J1","TerminalBlock:TerminalBlock_bornier-2_P5.08mm","C474881"
"Debug","J2","Connector_PinHeader_2.54mm:PinHeader_2x05_P2.54mm_Vertical","C124387"
"X_MOT","J3","Connector_JST:JST_XH_B4B-XH-A_1x04_P2.50mm_Vertical","C144395"
"E_MOT","J4","Connector_JST:JST_XH_B4B-XH-A_1x04_P2.50mm_Vertical","C144395"
"Amphenol","J5","Connector_USB:USB_Micro-B_Amphenol_10118194_Horizontal","C132563"
"Screw_Terminal_01x06","J6","TerminalBlock:TerminalBlock_bornier-6_P5.08mm","C8379"
"A_MOT","J7","Connector_JST:JST_XH_B4B-XH-A_1x04_P2.50mm_Vertical","C144395"
"Y_MOT","J8","Connector_JST:JST_XH_B4B-XH-A_1x04_P2.50mm_Vertical","C144395"
"Display","J9","Connector_IDC:IDC-Header_2x05_P2.54mm_Vertical","C429962"
"X-STOP","J10","Connector_JST:JST_XH_B2B-XH-A_1x02_P2.50mm_Vertical","C158012"
"A-STOP","J11","Connector_JST:JST_XH_B2B-XH-A_1x02_P2.50mm_Vertical","C158012"
"Z_MOT","J12","Connector_JST:JST_XH_B4B-XH-A_1x04_P2.50mm_Vertical","C144395"
"B_MOT","J13","Connector_JST:JST_XH_B4B-XH-A_1x04_P2.50mm_Vertical","C144395"
"Y-STOP","J14","Connector_JST:JST_XH_B2B-XH-A_1x02_P2.50mm_Vertical","C158012"
"B-STOP","J15","Connector_JST:JST_XH_B2B-XH-A_1x02_P2.50mm_Vertical","C158012"
"Z-STOP","J16","Connector_JST:JST_XH_B2B-XH-A_1x02_P2.50mm_Vertical","C158012"
"Fan_Filament","J17","Connector_JST:JST_XH_B2B-XH-A_1x02_P2.50mm_Vertical","C158012"
"Bed_Th","J18","Connector_JST:JST_XH_B2B-XH-A_1x02_P2.50mm_Vertical","C158012"
"Fan_Ctrl","J19","Connector_JST:JST_XH_B2B-XH-A_1x02_P2.50mm_Vertical","C158012"
"Ext_Th","J20","Connector_JST:JST_XH_B2B-XH-A_1x02_P2.50mm_Vertical","C158012"
"Opt_PwrA","J21","Connector_PinHeader_2.54mm:PinHeader_1x01_P2.54mm_Vertical","C2685179"
"Opt_PwrB","J22","Connector_PinHeader_2.54mm:PinHeader_1x01_P2.54mm_Vertical","C2685179"
"SolderJumper_2_Open","JP1, JP2, JP3, JP4, JP5, JP6, JP7, JP8, JP9, JP10, JP11, JP12, JP13, JP14, JP15, JP16, JP17, JP18, JP19, JP20","Jumper:SolderJumper-2_P1.3mm_Open_TrianglePad1.0x1.5mm",""
"39nH","L1","Inductor_SMD:L_0603_1608Metric","C74308"
"15uH","L2","Inductor_SMD:L_Taiyo-Yuden_MD-5050","C135291"
"AO3401A","Q1","Package_TO_SOT_SMD:SOT-23","C15127"
"WSF3087","Q2","Package_TO_SOT_SMD:TO-252-3_TabPin2","C2758420"
"WSF3087","Q3","Package_TO_SOT_SMD:TO-252-3_TabPin2","C2758420"
"AO3400A","Q4, Q5, Q6","Package_TO_SOT_SMD:SOT-23","C20917"
"10k","R1, R2, R3, R4, R5, R8, R9, R10, R11, R19, R24, R26, R27, R29, R31, R32, R33, R34, R35, R37, R41, R42, R43, R44, R45, R46, R47, R48, R49, R50, R51, R56, R57, R58, R59, R60, R61, R62, R63, R64, R65, R66, R68","Resistor_SMD:R_0402_1005Metric","C144807"
"100","R6, R25, R28","Resistor_SMD:R_0402_1005Metric","C106232"
"100k","R7, R17","Resistor_SMD:R_0402_1005Metric","C144732"
"100m","R12, R13, R14, R15, R36, R38, R39, R40, R52, R53, R54, R55","Resistor_SMD:R_0603_1608Metric","C247025"
"240","R16","Resistor_SMD:R_0402_1005Metric","C131545"
"24k","R18","Resistor_SMD:R_0402_1005Metric","C144775"
"33","R20, R21, R22, R23","Resistor_SMD:R_0402_1005Metric","C138002"
"3.3k","R30","Resistor_SMD:R_0402_1005Metric","C137992"
"4.7k","R67, R69","Resistor_SMD:R_0402_1005Metric","C105871"
"10k","RV1, RV2, RV3, RV4, RV5, RV6","Potentiometer_SMD:Potentiometer_Bourns_3224W_Vertical","C81348"
"SW_SPDT","SW1","Button_Switch_SMD:SW_SPDT_PCM12","C221841"
"SW_Push","SW2, SW3","Button_Switch_SMD:SW_SPST_B3U-1000P","C231329"
"TestPoint","TP1, TP2, TP3, TP4, TP5, TP6, TP7, TP8, TP9, TP10, TP11, TP12, TP13, TP14, TP17, TP18, TP19, TP20, TP21, TP22","TestPoint:TestPoint_Pad_D2.0mm",""
"A4988","U1, U2, U6, U7, U10, U11","Package_DFN_QFN:QFN-28-1EP_5x5mm_P0.5mm_EP3.35x3.35mm_ThermalVias","C38437"
"TPS5430DDA","U3","Package_SO:TI_SO-PowerPAD-8_ThermalVias","C9864"
"STM32F401RCT6","U4","Package_QFP:LQFP-64_10x10mm_P0.5mm","C74524"
"AMS1117-3.3","U5","Package_TO_SOT_SMD:SOT-223-3_TabPin2","C6186"
"USBLC6-2SC6","U8","Package_TO_SOT_SMD:SOT-23-6","C2827654"
"TC4427","U9","Package_SO:SOIC-8-1EP_3.9x4.9mm_P1.27mm_EP2.29x3mm","C20551"
"16MHz","Y1","Crystal:Crystal_SMD_3225-4Pin_3.2x2.5mm","C13738"

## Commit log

2022-03-15 Added KiCAD files
2022-03-15 Added Assembly & Gerber files
